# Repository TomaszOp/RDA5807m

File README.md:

# RDA5807m

Eagle module rda50807m library <br>
project pcb to raster 2.54 mm <br>

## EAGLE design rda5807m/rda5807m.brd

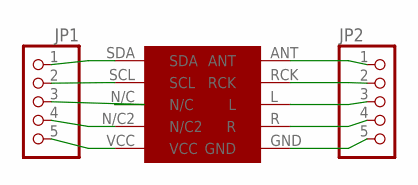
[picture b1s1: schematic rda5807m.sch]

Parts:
JP1, JP2: PINHD-1X5; 1X05
U$1: RDA

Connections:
GND: JP2.5, U$1.GND
unnamed: JP1.1, U$1.SDA
unnamed: JP1.2, U$1.SCL
unnamed: JP1.3, U$1.N/C
unnamed: JP1.4, U$1.N/C2
unnamed: JP1.5, U$1.VCC
unnamed: JP2.4, U$1.R
unnamed: JP2.3, U$1.L
unnamed: JP2.2, U$1.RCK
unnamed: JP2.1, U$1.ANT

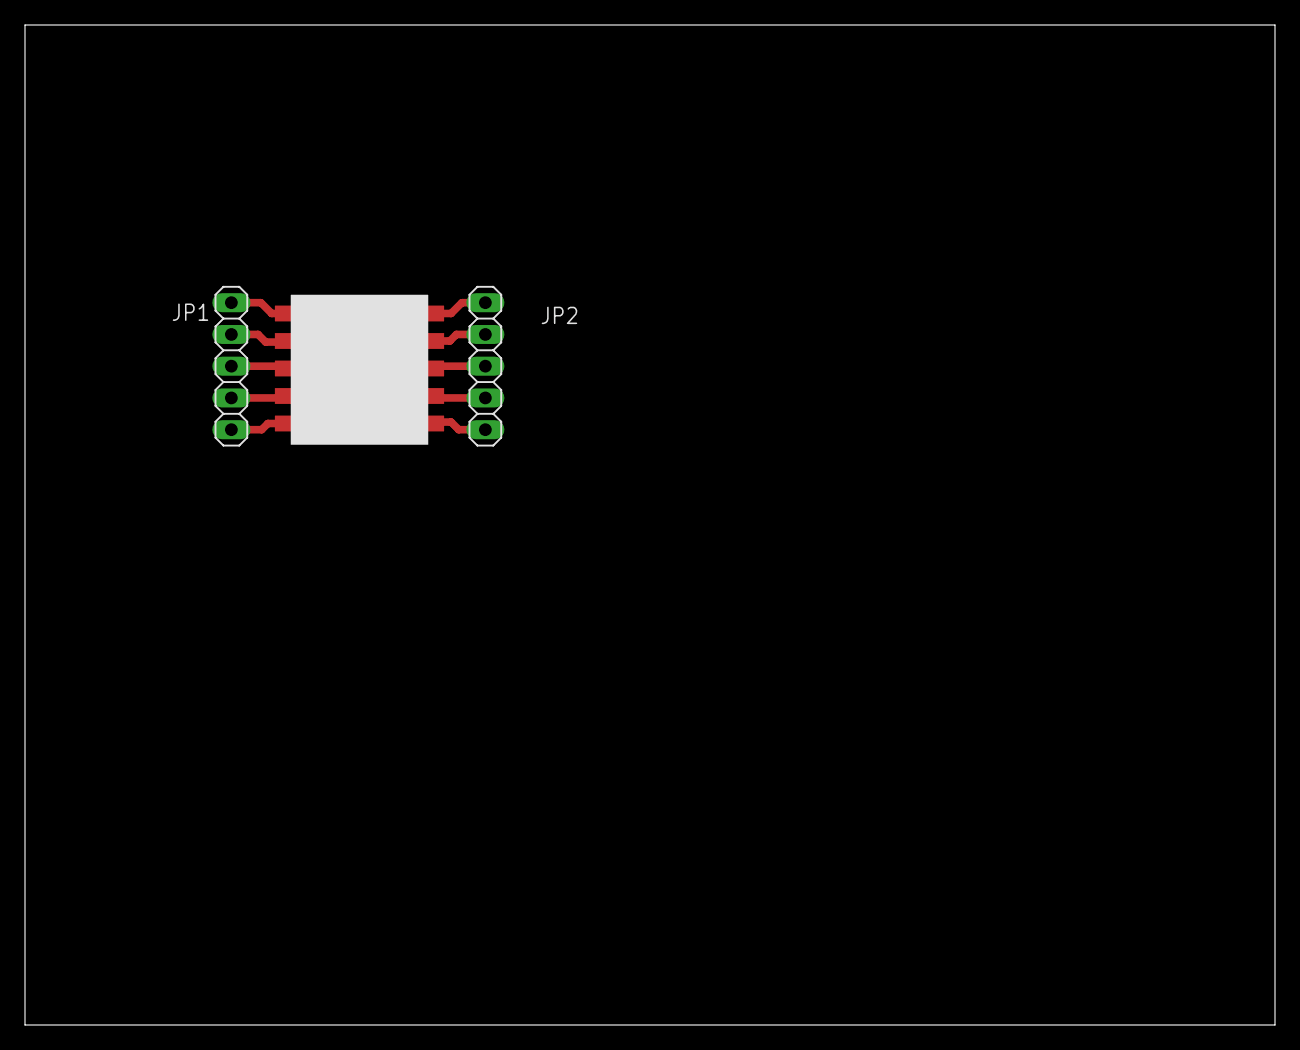
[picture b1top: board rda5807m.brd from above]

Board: 2 copper layers, 100.0 x 80.0 mm, 3 parts (0 on the bottom side), 10 nets.
